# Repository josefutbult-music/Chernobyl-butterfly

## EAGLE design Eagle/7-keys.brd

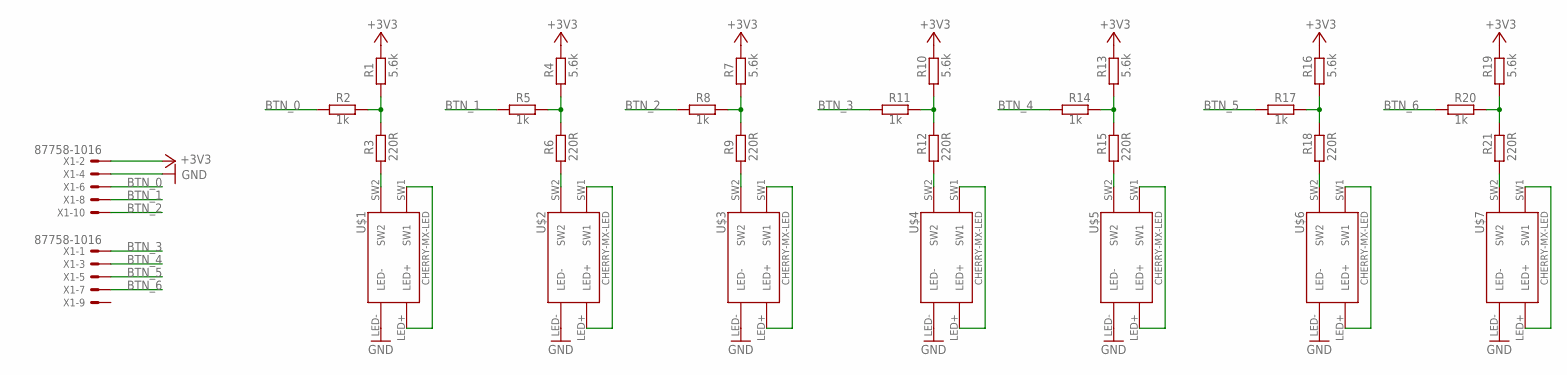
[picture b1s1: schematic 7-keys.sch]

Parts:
R1, R4, R7, R10, R13, R16, R19: 5.6k; R0603
R2, R5, R8, R11, R14, R17, R20: 1k; R0603
R3, R6, R9, R12, R15, R18, R21: 220R; R0603
U$1, U$2, U$3, U$4, U$5, U$6, U$7: CHERRY-MX-LED
X1: 87758-1016

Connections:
+3V3: R1.2, R4.2, R7.2, R10.2, R13.2, R16.2, R19.2, X1.2
BTN_0: R2.1, X1.6
BTN_1: R5.1, X1.8
BTN_2: R8.1, X1.10
BTN_3: R11.1, X1.1
BTN_4: R14.1, X1.3
BTN_5: R17.1, X1.5
BTN_6: R20.1, X1.7
GND: U$1.LED-, U$2.LED-, U$3.LED-, U$4.LED-, U$5.LED-, U$6.LED-, U$7.LED-, X1.4
unnamed: R1.1, R2.2, R3.2
unnamed: R3.1, U$1.SW2
unnamed: U$1.LED+, U$1.SW1
unnamed: R4.1, R5.2, R6.2
unnamed: R6.1, U$2.SW2
unnamed: U$2.LED+, U$2.SW1
unnamed: R7.1, R8.2, R9.2
unnamed: R9.1, U$3.SW2
unnamed: U$3.LED+, U$3.SW1
unnamed: R10.1, R11.2, R12.2
unnamed: R12.1, U$4.SW2
unnamed: U$4.LED+, U$4.SW1
unnamed: R13.1, R14.2, R15.2
unnamed: R15.1, U$5.SW2
unnamed: U$5.LED+, U$5.SW1
unnamed: R16.1, R17.2, R18.2
unnamed: R18.1, U$6.SW2
unnamed: U$6.LED+, U$6.SW1
unnamed: R19.1, R20.2, R21.2
unnamed: R21.1, U$7.SW2
unnamed: U$7.LED+, U$7.SW1

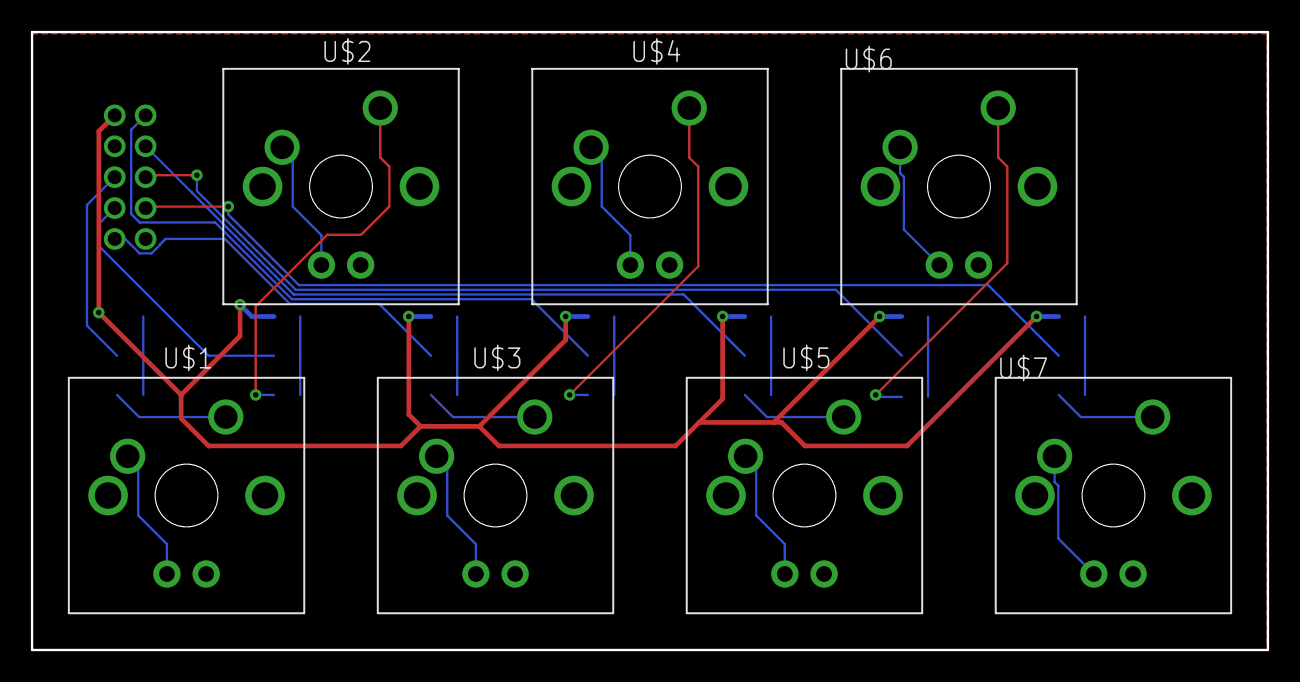
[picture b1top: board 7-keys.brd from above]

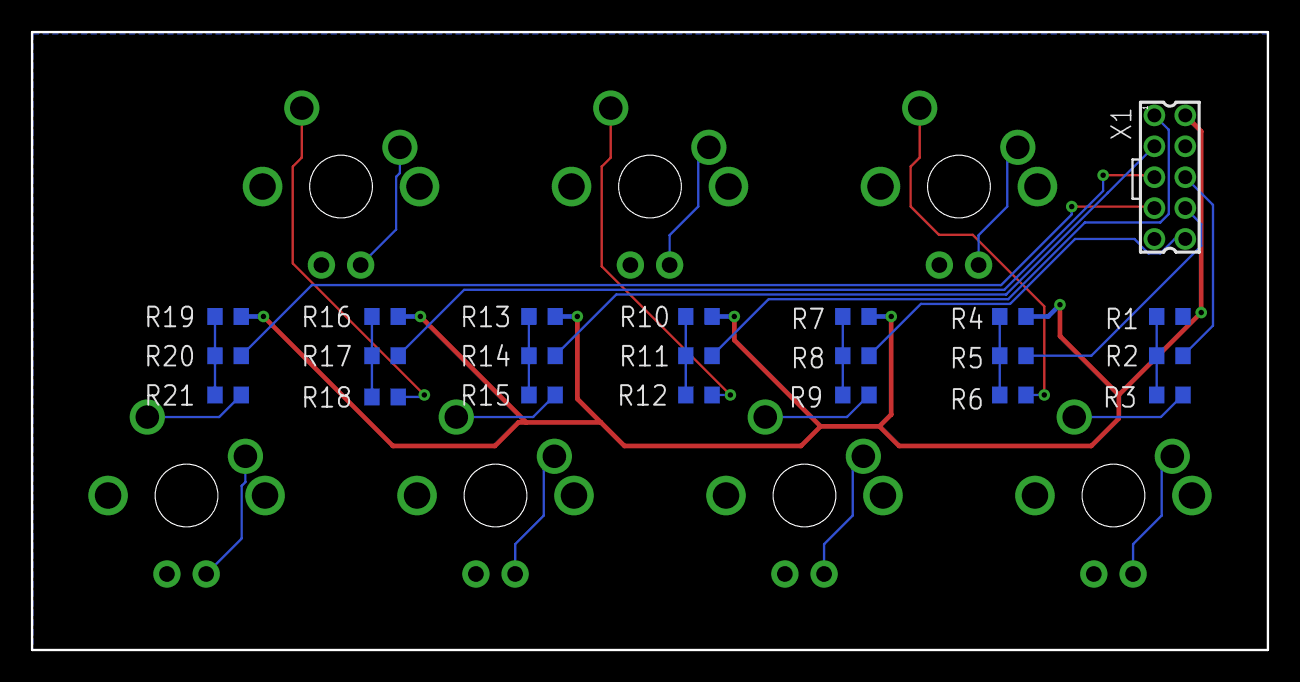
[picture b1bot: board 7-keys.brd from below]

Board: 2 copper layers, 80.0 x 40.0 mm, 29 parts (22 on the bottom side), 30 nets.

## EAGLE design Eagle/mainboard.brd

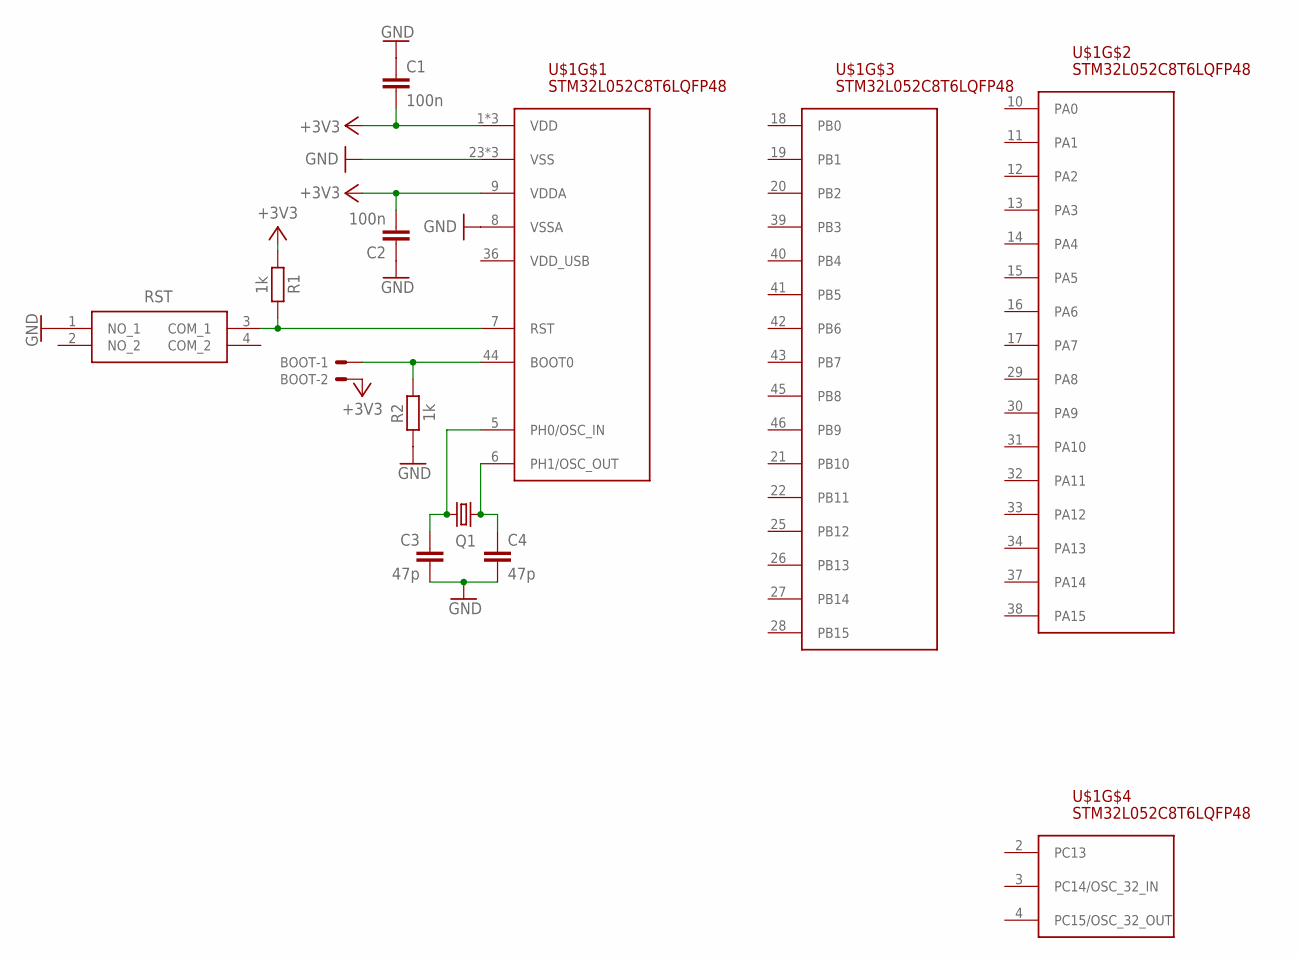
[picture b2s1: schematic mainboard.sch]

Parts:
BOOT: 87758-0216
C1, C2: 100n; 0603
C3, C4: 47p; 0603
Q1: CRYSTALHC49U70; HC49U70; MPN1 LFXTAL003240
R1, R2: 1k; R0603
RST: BUTTON; PTS647SK38SMTR2LFS
U$1: STM32L052C8T6LQFP48; QFP50P900X900X160-48N

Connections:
+3V3: BOOT.2, C1.2, C2.2, R1.1, U$1.1 (VDD), U$1.9 (VDDA), U$1.24 (VDD), U$1.48 (VDD)
GND: C1.1, C2.1, C3.2, C4.2, R2.1, RST.1 (NO_1), U$1.8 (VSSA), U$1.23 (VSS), U$1.35 (VSS), U$1.47 (VSS)
unnamed: R1.2, RST.3 (COM_1), U$1.7 (RST)
unnamed: BOOT.1, R2.2, U$1.44 (BOOT0)
OSC1: C4.1, Q1.2, U$1.6 (PH1/OSC_OUT)
OSC2: C3.1, Q1.1, U$1.5 (PH0/OSC_IN)
VDD_USB: U$1.36 (VDD_USB)

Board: 2 copper layers, 10 parts (0 on the bottom side), 6 nets, no tracks yet.

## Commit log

2021-03-01 Init
